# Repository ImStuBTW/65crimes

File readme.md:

# 65 Crimes, a CH559L FAK Keyboard

This is a 65% keyboard with the heart of a 40% keyboard. Nothing here is standard. It's not ergonomic. I have to be breaking some sort of keyboard law here. Welcome to the 65 Crimes.

The 65 Crimes is my take on a small row-staggered keyboard design. I've been getting into retro computing a bit more lately, and I wanted a non-ergonomic non-split keyboard design that didn't rely on a ton of layers. The 65 Crimes can play TiE-Fighter with the `F1`-`F12` keys being the only thing you need to hold `Fn` down for. I still wanted the keyboard to be compact and tweet however, so there's a few odd quirks going on here. The left row has been shaved down by half a key width. `Tab`, `Caps Lock`, and `Left Shift` all get downgraded from 1.5u to 1u, 1.75u to 1.25u, and 2.25u to 1.75u. Much more striking however is the number row. Rather than sticking with the popular compact 65% keyboard block design, I gave the number row a bit of breathing room. It's spaced out similar to a traditional function row. It makes it a little odd to type on, but the end result is a 65% keyboard that looks like a 75% keyboard at first glance.

I tackled a few personal firsts on this keyboard design. It's my first row-staggered keyboard, my first keyboard with spacebar stabilizers, my first keyboard with an onboard microcontroller, and my first time working with the FAK keyboard firmware. Everything worked out in the end, but there were a lot of layered learning experiences here.

## The Ergogen Layout

This one's going to take some explaining.

Ergogen is a keyboard layout generator designed to make ergonomic keyboards. It's right there in the name! It's designed to make "column staggered" keyboards where all of the keys in a column (QAZ, WSX, etc.) are aligned together. This is a traditional "row staggered" keyboard. It's ostensibly less ergonomic. It's also something Ergogen is *really* not designed for.

To design the 65 Crimes keyboard I decided to get a little creative. The Ergogen config file for this board literally turns it on its head. Everything is rotated 90 degrees so that it just looks like an excessively tall column staggered keyboard. Rather than a 15 column, 5 row keyboard, Ergogen thinks it's designing a 5 column, 15 row keyboard.

The approach takes a bit to wrap your head around. X becomes Y, length becomes width, and straightforward becomes tedious. This is definitely a case of, "When you have a hammer, everything looks like a nail". If you're familiar with Ergogen then this approach is still probably faster than learning another tool. If you're looking to learn Ergogen to make a row-staggered keyboard however, you're probably better off looking at some of the [other](https://github.com/jeroen94704/klepcbgen) [tools](https://kb.xyz.is) out there. There are also some [Ergogen keyboards examples](https://github.com/Woovie/seven-five) out there which manage a row-staggered layout without this rotation approach. This is just what happened to work for me.

## The PCB

At its core, the 65 Crimes keyboard was an excuse to learn more about building keyboards with built in microcontrollers. The Arduino Pro Micro, RP2040, Nice!Nano, and XIAO boards are great, but it's hard to beat some of the minimalist designs you can build when you're not trying to hide a large postage stamp sized microcontroller somewhere. I briefly explored some of the options out there for built in microcontrollers, but they all seemed to have a level of complexity I wasn't ready to dive into. I got fairly far along looking at STM32-based designs, but the programming headers just seemed like a headache I didn't want to deal with.

Enter the CH55X line of chips. These budget microcontrollers became popular during the Covid era chip storage. They're not going to win any performance contests, but they're cheap, easy to source, and have onboard USB support. The later is naturally beneficial for keyboard builders, but there's a few other nice touches here. CH55X chips have fairly simple circuit designs. You only need two resistors, two capacitors, two buttons, an ESD protection chip, and a USB port to get these chips up and running. These chips are also completely hand-solderable if you'd like to skip an expensive PCBA assembly step. Even the basic flashing is nice and straightforward. The same USB port you use for connecting to the keyboard is used for flashing the firmware. (Similar to an Arduino Pro Micro.) Instead of tapping the reset button twice, you simply need to add and hold down a dedicated "Boot" button.

The majority of keyboards with CH55X chips are using the smaller CH552T chip. It has a nice hand-solderable 0.65mm pitch chip package. Unfortunately, it doesn't have enough pins for the 65 Crimes large 67 key layout. Thankfully the CH559L has more than enough pins for this design. Things get a little trickier on the hand soldering front however. The CH559L has a tighter 0.5mm pitch. It's nothing a little flux can't deal with, but you may want to buy a few spares if this is your first time working with SMD soldering.

Again, this is my first time working with an onboard microcontroller or the CH55X family of chips. All of the pinouts and component choices are shamelessly copied from semickolon's [Partycrasher Micro](https://oshwlab.com/kkpjfobj/partycrasher-micro) microcontroller design.

## The Firmware

One slight catch with the CH55X chips is that they can't run most of the popular keyboard firmwares. QMK and ZMK won't run on this particular microcontroller. Instead, the 65 Crimes leverages the relatively new [FAK keyboard](https://github.com/semickolon/fak) firmware.

I didn't dive deep into its capabilities, but my first impression of FAK has been great. It's a declarative keyboard firmware that should be familiar for anyone who's worked with ZMK. It's nice having a purely functional firmware which throws errors at compile time if you've accidentally made an issue with your keyboard config.

FAK can be built locally on your computer, but they also offer a preconfigured Github Codespace as a build environment. It makes things nice and simple to get your first firmware up and running. The only package you need to run locally is the flashing utility `wchisp`, which offers precompiled binaries for Windows, Mac, and Linux.

The keymap for 65 Crimes can be found in this repository's `/fak-config` folder. I haven't used any FAK features other than layers to enable a basic `Fn` key. For more advanced ergo keyboards however, FAK supports all the usual macros, combos, encoders, split keyboards, mouse keys, sticky layers, and tap dancing you're accustomed to. Their [Discord](https://discord.gg/4Ev8GFZNR2) was incredibly welcoming and patient with all my questions.

## The Switch Plates

The 65 Crimes keyboard is also the first time I've designed a keyboard layout that uses stabilizers. These are those small metal bars which help wide keys press down evenly without any wobble. They're ubiquitous in the world of row staggered MX keyboards, but a bit less common in the Choc space.

Choc stabilizers require a switch plate. The plastic anchors need to be sandwiched between two layers of PCB (or other stiff material) to seat correctly. Thankfully Ergogen makes it pretty straightforward to make a switch plate. Fire up your PCB's outline, cut out a 14mm hole on each switch, add the stabilizer cutouts, drop in some mounting holes, and bam you're done. Unfortunately the 65 Crimes is a somewhat large keybaord by split ergonomic standards. JLCPCB wanted another $15 USD for the full switch plate.

I experimented with making a cheaper stabilizer "shim". This was a smaller piece of PCB material that only covered the spacebar keys and the left and right modifiers next to them. The idea was that you could print off this smaller piece and save a few bucks during your prototyping.

The actual stabilizer footprints come from a design put together by [FKCaps](https://github.com/FKcaps/mbk-footprints/tree/main). The cutout isn't symmetrical with the key switch and is aligned closer to the top edge. This resulted in the shim having a relatively thin piece of PCB material. JLCPCB wanted an extra $7 USD to make sure the hole was routed properly. Rather than iterating on this design further, I went ahead and just printed out the full switch plate. The switch plate worked great the first time thankfully, but I'm leaving the shim designs in here for anyone who's interested.

For this particular build I went with [Chosfox's CFX WoB Keycap Set](https://chosfox.com/collections/low-profile-keycaps/products/chocfox-wob). I wanted a keycap set with legends, and this layout used a few odd sized 1.25u and 1.75u keycaps for the modifiers, tab, and enter key. This left Chosfox as pretty much the only game in town. The keycap set is split into an Alpha, Ergo, and Extras kit. I was *barely* able to squeak by with just the Alpha and Ergo kits.

The Ergo CFX kit comes with two 2u spacebar keys. It also comes with a 2u key labeled "Shift". There are also two bright orange 3u spacebar keys. I asked around online and didn't get many strong opinions when it came to using three 2u spacebars or two 3u spacebars.

My final design went with three 2u spacebars. This mostly came down to parts sourcing. It turns out the 3u Choc stabilizers are *really* hard to source right now. I ended up getting five 2u Choc stabilizers from [LowProKB.ca](https://lowprokb.ca/collections/parts/products/kailh-choc-stabilizers) for about $5 USD plus $7 USD shipping. I could have purchased 3u stabilizer wires from [CannonKeys](https://cannonkeys.com/products/stabilizer-wires?variant=40921516540015) for $4 USD plus $4 USD shipping if I really wanted to use the larger 3u CFX keycaps. Instead, I just ended up purchasing three [MBK 2u convex spacebars](https://lowprokb.ca/products/mbk-low-profile-pbt-blank-keycaps?variant=44794533707940) from LowProKB for an extra $3 USD. It sounds a little silly to say I went with three 2u spacebars to save $5 USD, but I already happened to have a matching purple Esc key from an earlier FK Custom order.

It's worth noting that these Chosfox keycaps use their "CFX" spacing *only on their 1u keycaps*. These CFX keycaps have become popular for minimally spaced keyboards. Standard MBK keycaps are 18mm x 17mm, while the CFX keycaps are a square 17mm x 17mm. That's a free 14mm of saved width on a keyboard like this. Unfortunately the other 1.25u, 1.5u, 1.75u, and 2u keycaps stick to their standard MBK spacing. (That is to say the 1.5u keycap is 18mm * 1.5 = 27mm wide.) For that reason this keyboard sticks to standard Choc spacing.

The `footprints` folder contains several custom footprints. Getting the spacing right on this was tricky, so I created a full line of `choc-Xu` footprints to show their exact spacing on the PCB. The `choc-stab-2u` and `choc-stab-2u-cutout` footprints are based on footprint designs by [FKCaps](https://github.com/FKcaps/mbk-footprints/tree/main).

## The Case

After all the other experimentation with this keyboard, I stuck with what has worked for me in the past with the 65 Crimes case design. It uses my standard "Tray" design. The PCB and switch plate have mounting holes, and the case has standoff legs with heat set inserts. The only thing I did different this time was splitting the case in half to fit on my printer, and making the sides of the case a bit taller on the top and sides for aesthetic purposes. I also decided to fire up Cura's "Fuzzy Skin" setting.

## The Build (and Lessons Learned)

No long build guide this time unfortunately. There were a few false starts and fiddling with this keyboard, so I don't have step-by-step pictures to share. Overall the build went smoothly. The CH559L was the trickiest piece to solder. You need to line it up precisely, apply a bit of solder flux to one side, then quickly apply a bit of solder while the chip is still aligned. Once one of the legs is soldered properly, you can drag-solder the rest as you would with any other SMD component. The same approach goes for the USB-C port. The ESD protection chip, two capacitors, and two resistors should be a bit more straightforward.

This wasn't my first rodeo when it came to working with SMD parts. Thankfully the TypePak has similar sized components with just as tiny pitches. One slightly embarrassing learning experience was to *not trust the orientation of text on SMD packages*. I totally fried some of the ESD and CH559L chips by having things oriented the wrong way.

The "rotate everything 90 degrees in Ergogen" trick also nearly came back to bite me. It turns out swapping the col and row pinout definitions wasn't enough to compensate for its rotated definition. All of the diodes on this keyboard are technically "backwards" from how I typically build them. Thankfully it didn't lead to anything more complicated than needing to swap the "ColToRow" variable in the FAK firmware to "RowToCol".

Overall the 65 Crimes was a great learning experience. Row staggering with Choc spacing has taken me a bit more getting used to than I expected. The function row styled number keys have been a fun novelty, but they're a little tricky to use in practice. The keys one would use from gaming on the left side of the keyboard aren't too hard to build some muscle memory for, but I almost always tap the wrong number when dealing with 7, 8, or 9. I've still got a few CH559L chips I managed not to try, so I'm looking forward to doing a bit more experimenting with FAK in the future!

## Build of Materials

| Part                       | Amount | Price       | Link |
| -------------------------- | ------ | ----------- | ---- |
| 65 Crimes PCB via JLCPCB   | 1      | $35 USD Shipped (Shim), $50 USD Shipped (Switchplate) | https://github.com/ImStuBTW/65crimes |
| CH559L                     | 1      | $8 USD (For 5) | https://www.aliexpress.us/item/3256804321719097.html |
| Mid-Mount USB              | 1      | $1.00 USD   | https://www.aliexpress.us/item/3256805368744698.html |
| 5.1K Resistors             | 2      | $3.50 USD (Multi-Pack)   | https://www.aliexpress.us/item/3256806698117192.html |
| 3.3uf Cap                  | 1      | $1.00 USD   | https://www.aliexpress.us/item/3256806243569846.html |
| 100nf Cap                  | 1      | $2.00 USD (Multi-Pack)   | https://www.aliexpress.us/item/3256805970706203.html |
| USBLC6-2SC6 ESD Protection | 1      | $1.50 USD   | https://www.aliexpress.us/item/2251832337465783.html |
| 1N4148 T4 Diodes           | 67     | $2.00 USD   | https://www.aliexpress.us/item/2255800498728983.html |
| Choc Switches              | 67     | $45.00 USD  | https://lowprokb.ca/collections/switches/products/kailh-choc-low-profile-switches |
| Chocfox CFX Keycaps        | Alphas + Mods | $60.00 USD | https://chosfox.com/collections/low-profile-keycaps/products/chocfox-wob?variant=42753190461634 |
| MBK Spacebars (Optional)   | 3      | $3.00 USD   | https://lowprokb.ca/collections/keycaps/products/mbk-low-profile-pbt-blank-keycaps?variant=44794533511332 |
| 4mm M2 Screws              | 8      | $1.00 USD   | https://www.aliexpress.us/item/2255801062616407.html |
| M2 Screw Inserts           | 8      | $1.50 USD   | https://www.aliexpress.us/item/3256804349544912.html |
| Bumpons                    | 1 Pack | $10.00 USD  | https://www.amazon.com/Adhesive-Bumper-106-PC-Spherical-Square/dp/B06XPCLN23/ |

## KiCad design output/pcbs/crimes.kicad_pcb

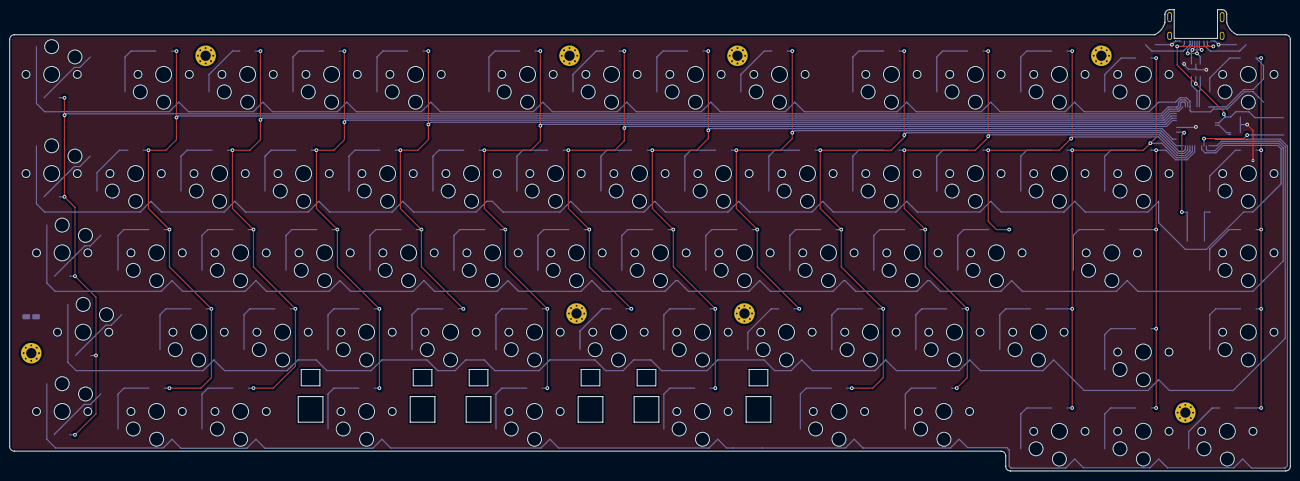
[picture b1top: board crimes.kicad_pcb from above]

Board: 2 copper layers, 274.5 x 98.9 mm, 147 parts (1 on the bottom side), 92 nets.

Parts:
B1, B2: SW_TACT_ALPS_SKQGABE010
D1, D2, D3, D4, D5, D6, D7, D8, D9, D10, D11, D12, D13, D14, D15, D16, D17, D18, D19, D20, D21, D22, D23, D24, D25, D26, D27, D28, D29, D30, D31, D32, D33, D34, D35, D36, D37, D38, D39, D40, D41, D42, D43, D44, D45, D46, D47, D48, D49, D50, D51, D52, D53, D54, D55, D56, D57, D58, D59, D60, D61, D62, D63, D64, D65, D66, D67, D68: ComboDiode
MCU1: LQFP-48_7x7mm_P0.5mm
S1, S2, S3, S4, S5, S6, S7, S8, S9, S10, S11, S12, S13, S14, S15, S16, S17, S18, S19, S20, S21, S22, S23, S24, S25, S26, S27, S28, S29, S30, S31, S32, S33, S34, S35, S36, S37, S38, S39, S40, S41, S42, S43, S44, S45, S46, S47, S48, S49, S50, S51, S52, S53, S54, S55, S56, S57, S58, S59, S60, S61, S62, S63, S64, S65, S66, S67, S68: PG1350
_1, _2, _3, _4, _5, _6, _7, _8: MountingHole_2.2mm_M2_Pad_Via

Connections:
BOOT: B1.1, MCU1.16
GND: B1.2, MCU1.18
RST: B2.1, MCU1.3
VBUS: B2.2, MCU1.41
bottom_backspace: D50.2, S53.2
bottom_eight: D46.2, S49.2
bottom_equals: D49.2, S52.2
bottom_escape: D65.2, S65.2
bottom_five: D43.2, S46.2
bottom_four: D42.2, S45.2
bottom_nine: D47.2, S50.2
bottom_one: D39.2, S42.2
bottom_seven: D45.2, S48.2
bottom_six: D44.2, S47.2
bottom_special: D51.2, S54.2
bottom_three: D41.2, S44.2
bottom_two: D40.2, S43.2
bottom_zero: D48.2, S51.2
col1: D62.1, D63.1, D64.1, D65.1, D66.1, MCU1.27
col2: D1.1, D12.1, D26.1, D39.1, D52.1, MCU1.26
col3: D2.1, D13.1, D27.1, D40.1, D53.1, MCU1.25
col4: D3.1, D14.1, D28.1, D41.1, D54.1, MCU1.24
col5: D4.1, D15.1, D29.1, D42.1, MCU1.23
col6: D5.1, D16.1, D30.1, D43.1, D55.1, MCU1.22
col7: D6.1, D17.1, D31.1, D44.1, MCU1.21
col8: D7.1, D18.1, D32.1, D45.1, D56.1, MCU1.13
col9: D8.1, D19.1, D33.1, D46.1, MCU1.12
col10: D9.1, D20.1, D34.1, D47.1, D57.1, MCU1.11
col11: D10.1, D21.1, D35.1, D48.1, D58.1, MCU1.10
col12: D11.1, D22.1, D36.1, MCU1.9
col13: D23.1, D49.1, D59.1, D67.1, MCU1.8
col14: D24.1, D37.1, D50.1, D60.1, MCU1.7
col15: D25.1, D38.1, D51.1, D61.1, D68.1, MCU1.36
home_backspace: D37.2, S64.2
home_dash: D36.2, S40.2
home_eight: D33.2, S37.2
home_escape: D64.2, S60.2
home_five: D30.2, S34.2
home_four: D29.2, S33.2
home_nine: D34.2, S38.2
home_one: D26.2, S30.2
home_seven: D32.2, S36.2
home_six: D31.2, S35.2
home_special: D38.2, S41.2
home_three: D28.2, S32.2
home_two: D27.2, S31.2
home_zero: D35.2, S39.2
mod_backspace: D60.2, S58.2
mod_equals: D59.2, S57.2
mod_escape: D66.2, S61.2
mod_five: D55.2, S67.2
mod_nine: D57.2, S62.2
mod_one: D52.2, S55.2
mod_seven: D56.2, S68.2
mod_special: D61.2, S59.2
mod_three: D54.2, S66.2
mod_two: D53.2, S56.2
mod_zero: D58.2, S63.2
num_backspace: D68.2, S14.2
num_dash: D11.2, S12.2
num_eight: D8.2, S9.2
num_equals: D67.2, S13.2
num_escape: D62.2, S1.2
num_five: D5.2, S6.2
num_four: D4.2, S5.2
num_nine: D9.2, S10.2
num_one: D1.2, S2.2
num_seven: D7.2, S8.2
num_six: D6.2, S7.2
num_three: D3.2, S4.2
num_two: D2.2, S3.2
num_zero: D10.2, S11.2
row1: MCU1.28, S1.1, S2.1, S3.1, S4.1, S5.1, S6.1, S7.1, S8.1, S9.1, S10.1, S11.1, S12.1, S13.1, S14.1
row2: MCU1.4, S15.1, S16.1, S17.1, S18.1, S19.1, S20.1, S21.1, S22.1, S23.1, S24.1, S25.1, S26.1, S27.1, S28.1, S29.1
row3: MCU1.2, S30.1, S31.1, S32.1, S33.1, S34.1, S35.1, S36.1, S37.1, S38.1, S39.1, S40.1, S41.1, S60.1, S64.1
row4: MCU1.1, S42.1, S43.1, S44.1, S45.1, S46.1, S47.1, S48.1, S49.1, S50.1, S51.1, S52.1, S53.1, S54.1, S65.1
row5: MCU1.48, S55.1, S56.1, S57.1, S58.1, S59.1, S61.1, S62.1, S63.1, S66.1, S67.1, S68.1
top_backspace: D24.2, S28.2
top_dash: D22.2, S26.2
top_eight: D19.2, S23.2
top_equals: D23.2, S27.2
top_escape: D63.2, S15.2
top_five: D16.2, S20.2
top_four: D15.2, S19.2
top_nine: D20.2, S24.2
top_one: D12.2, S16.2
top_seven: D18.2, S22.2
top_six: D17.2, S21.2
top_special: D25.2, S29.2
top_three: D14.2, S18.2
top_two: D13.2, S17.2
top_zero: D21.2, S25.2

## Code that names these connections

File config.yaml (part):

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      where: controller_parts_mcu
      params:
        side: 'B'
        P15: row5  # Pin 48
        P16: row4  # Pin  1
        P17: row3  # Pin  2
        P30: row2  # Pin  4
        P27: row1  # Pin 28
        P04: col15 # Pin 36
        P31: col14 # Pin  7
        P32: col13 # Pin  8
        P33: col12 # Pin  9
        P34: col11 # Pin 10
        P35: col10 # Pin 11
        P36: col9  # Pin 12
        P37: col8  # Pin 13
        P20: col7  # Pin 21
        P21: col6  # Pin 22
        P22: col5  # Pin 23
        P23: col4  # Pin 24
        P24: col3  # Pin 25
        P25: col2  # Pin 26
        P26: col1  # Pin 27
        P51: DPLUSOUT
        P50: DNEGOUT
      adjust:
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
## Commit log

2023-12-07 init commit
2024-03-02 Update with big and small options.
2024-03-02 Fixed Image
2024-03-02 Actually fixed image.
2024-05-19 Significant Updates
2024-05-19 Added Prototype Image.
2024-05-25 Updated Mounting Holes
2024-05-27 Updated Documentation.
2024-05-27 Updated Docs
2024-06-09 Fixed MCU Pinout
2024-07-01 Fixed Pinouts.
2024-07-02 Firmware Tweaks
2024-09-24 Fixed CH559L footprint silkscreen.
2024-09-24 Additional Images
2024-09-24 Added the CH559L Image.
2024-09-24 Swapped Header Image
2024-09-24 Swapped The Header Back
2024-09-24 Spelling? Checked!
2024-09-24 Another Typo
